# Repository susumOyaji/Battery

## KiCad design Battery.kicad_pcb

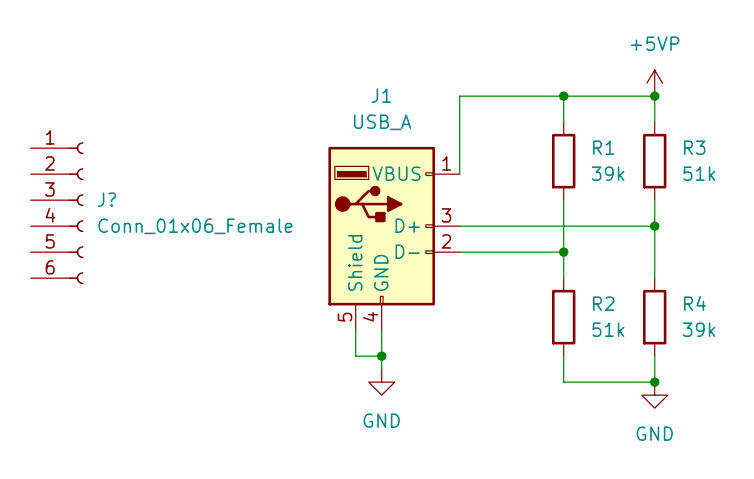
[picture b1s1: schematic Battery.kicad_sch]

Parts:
J1: USB_A; USB_A_Molex_67643_Horizontal
R1, R4: 39k; R_Axial_DIN0614_L14.3mm_D5.7mm_P20.32mm_Horizontal
R2, R3: 51k; R_Axial_DIN0614_L14.3mm_D5.7mm_P20.32mm_Horizontal

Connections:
+5VP: J1.1 (VBUS), R1.1, R3.1
GND: J1.4 (GND), J1.5 (Shield), R2.2, R4.2
unnamed: J1.2 (D-), R1.2, R2.1
unnamed: J1.3 (D+), R3.2, R4.1

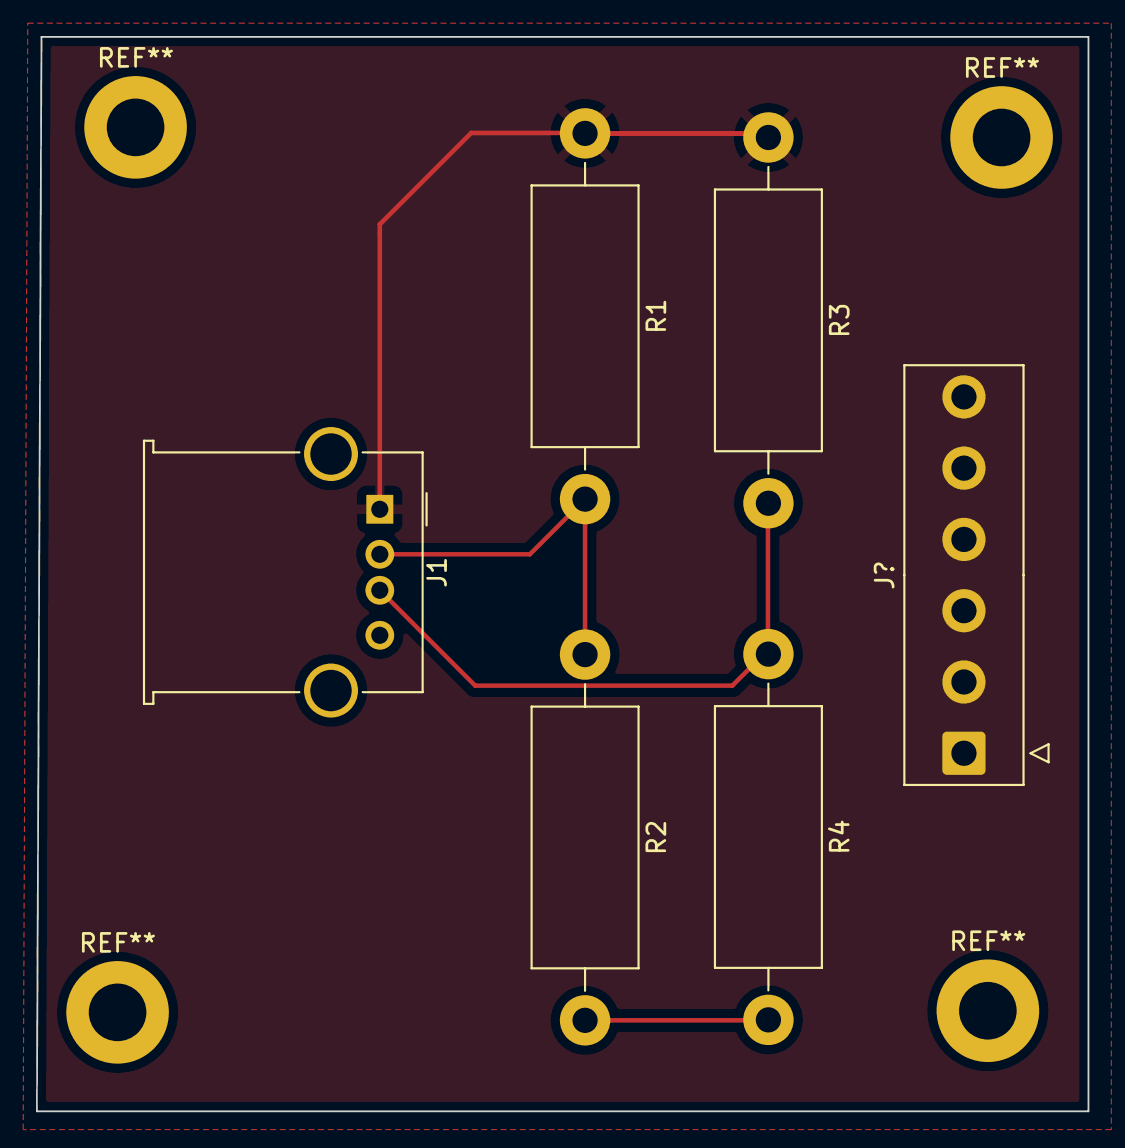
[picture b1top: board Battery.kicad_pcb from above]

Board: 2 copper layers, 58.4 x 59.7 mm, 6 parts (0 on the bottom side), 4 nets.

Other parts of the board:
J?: Conn_01x06_Female; TE_826576-6_1x06_P3.96mm_Vertical
